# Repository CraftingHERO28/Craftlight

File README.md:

## Overview

I designed and built a compact, cost-effective 3-level light indicator (bar graph) powered by an LM339 quad comparator. The core of the circuit relies on an LDR sensor combined with a precise voltage divider ladder to monitor ambient light levels and trigger three discrete LEDs accordingly. 

I deliberately chose an open-board THT (Through-Hole Technology) design without a 3D-printed or plastic enclosure. This decision keeps manufacturing costs low, prevents unwanted shadows or light reflections from distorting the LDR readings, gives me instant physical access to the trimmer potentiometer and coin cell battery holder, and showcases the clean, hand-soldered components and copper traces.

## Challenges Faced

* **Sensor Placement:** Finding the optimal layout geometry was tricky. I had to place the LDR far enough away from the output LEDs to prevent optical feedback, ensuring the LEDs wouldn't accidentally blind the sensor and cause erratic switching behavior.
* **Routing & DRC Clearance:** Managing the traces on a single-sided-friendly layout in KiCad required some patience. I had to carefully resolve a few initial Design Rule Checker (DRC) warnings regarding trace clearance and pad spacing before exporting the final Gerber files for JLCPCB production.
* **Component Footprint Selection:** Balancing aesthetic choices with practical assembly meant sorting out proper THT footprints, such as selecting horizontal axial resistors so the board stays flat, neat, and visually balanced.

*Translated with Google Translator*

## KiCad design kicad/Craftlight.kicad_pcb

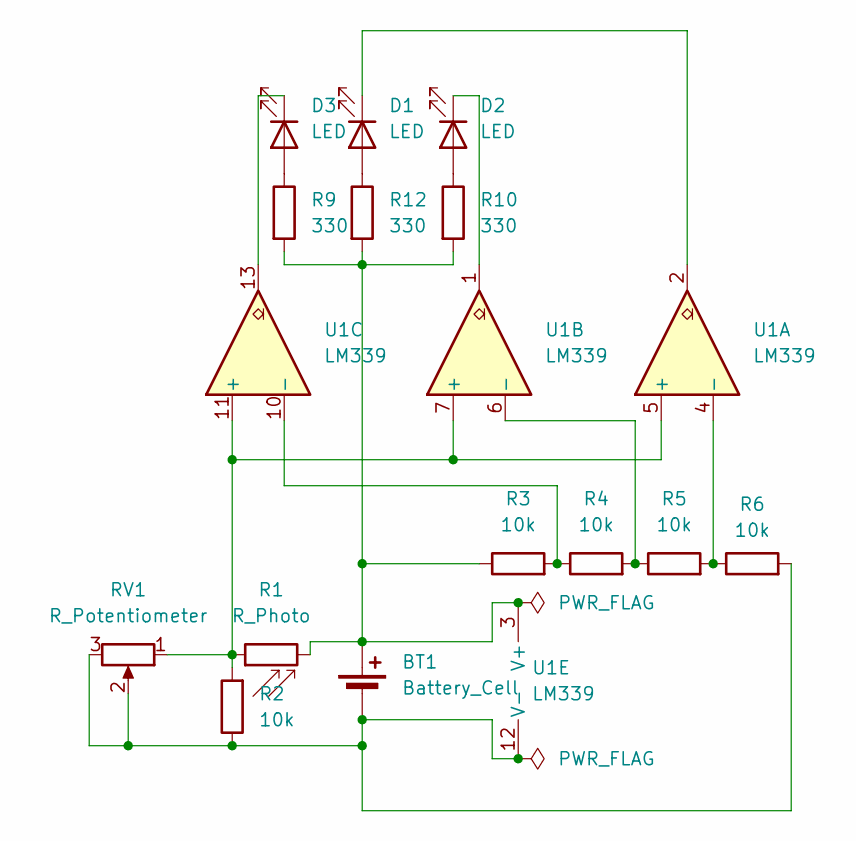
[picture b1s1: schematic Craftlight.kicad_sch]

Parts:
BT1: Battery_Cell; BatteryHolder_Keystone_106_1x20mm
D1, D2, D3: LED; LED_D3.0mm
R1: R_Photo; R_LDR_5.0x4.1mm_P3mm_Vertical
R2, R3, R4, R5, R6: 10k; R_Axial_DIN0207_L6.3mm_D2.5mm_P7.62mm_Horizontal
R9, R10, R12: 330; R_Axial_DIN0207_L6.3mm_D2.5mm_P7.62mm_Horizontal
RV1: R_Potentiometer; Potentiometer_Piher_PT-10-H01_Horizontal
U1: LM339; DIP-14_W7.62mm_Socket

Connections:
unnamed: BT1.1 (+), R1.2, R3.1, R9.2, R10.2, R12.2, U1.3 (V+)
unnamed: BT1.2 (-), R2.1, R6.2, RV1.2, RV1.3, U1.12 (V-)
unnamed: D1.2 (A), R12.1
unnamed: D1.1 (K), U1.2
unnamed: D2.2 (A), R10.1
unnamed: D2.1 (K), U1.1
unnamed: D3.2 (A), R9.1
unnamed: D3.1 (K), U1.13
unnamed: R1.1, R2.2, RV1.1, U1.5 (+), U1.7 (+), U1.11 (+)
unnamed: R5.2, R6.1, U1.4 (-)
unnamed: R4.2, R5.1, U1.6 (-)
unnamed: R3.2, R4.1, U1.10 (-)

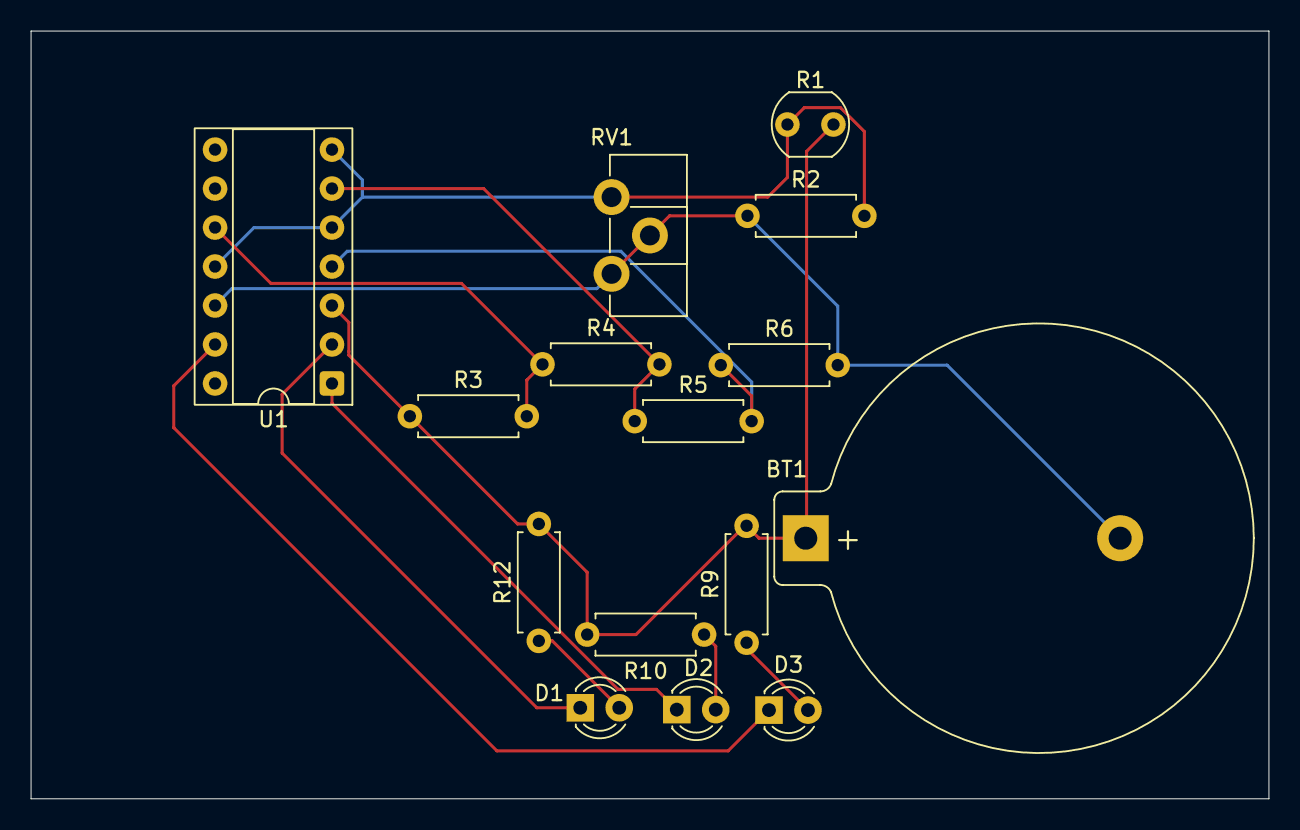
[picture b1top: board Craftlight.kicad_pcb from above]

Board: 2 copper layers, 80.7 x 50.0 mm, 15 parts (0 on the bottom side), 12 nets.
